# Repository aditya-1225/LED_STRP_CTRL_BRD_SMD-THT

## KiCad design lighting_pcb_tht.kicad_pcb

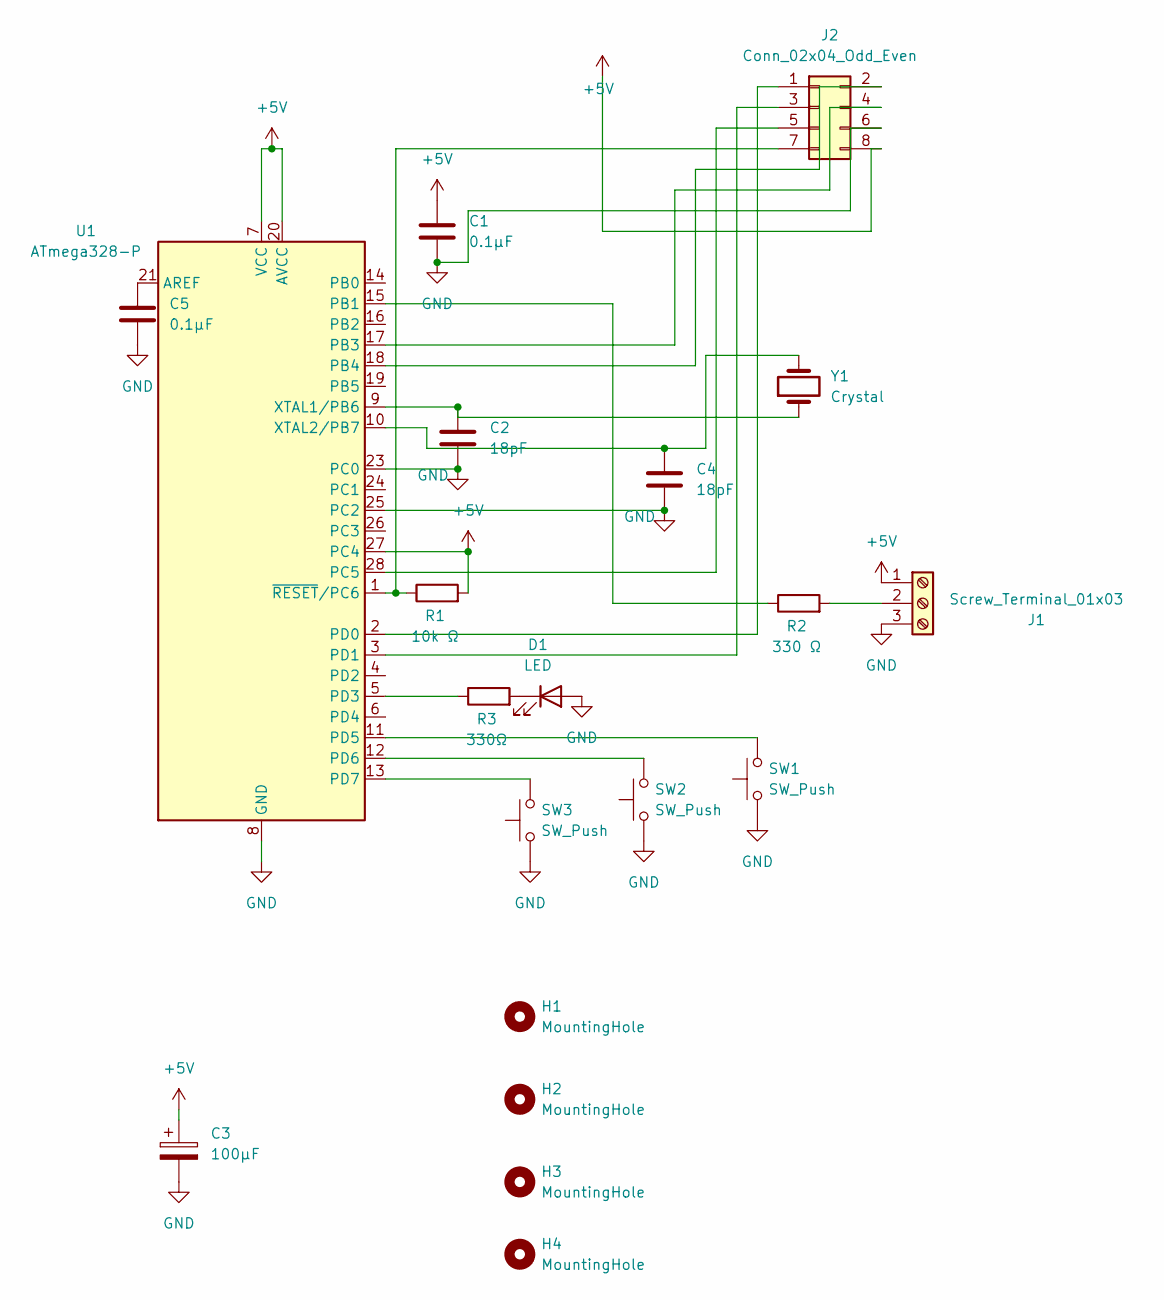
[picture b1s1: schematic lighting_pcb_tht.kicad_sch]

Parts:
C1, C5: 0.1μF; C_1206_3216Metric_Pad1.33x1.80mm_HandSolder
C2, C4: 18pF; C_1206_3216Metric_Pad1.33x1.80mm_HandSolder
C3: 100μF; CP_Radial_D5.0mm_P2.00mm
D1: LED; LED_1206_3216Metric_Pad1.42x1.75mm_HandSolder
H1, H2, H3, H4: MountingHole; MountingHole_2mm
J1: Screw_Terminal_01x03; TerminalBlock_MaiXu_MX126-5.0-03P_1x03_P5.00mm
J2: Conn_02x04_Odd_Even; PinHeader_2x04_P2.54mm_Vertical
R1: 10k Ω; R_1206_3216Metric_Pad1.30x1.75mm_HandSolder
R2: 330 Ω; R_1206_3216Metric_Pad1.30x1.75mm_HandSolder
R3: 330Ω; R_1206_3216Metric_Pad1.30x1.75mm_HandSolder
SW1, SW2, SW3: SW_Push; SW_PUSH-12mm
U1: ATmega328-P; DIP-28_W7.62mm_Socket
Y1: Crystal; Crystal_HC49-U_Vertical

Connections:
+5V: C1.1, C3.1, J1.1, J2.8, R1.2, U1.7 (VCC), U1.20 (AVCC), U1.27 (PC4)
GND: C1.2, C2.2, C3.2, C4.2, C5.2, D1.2 (A), J1.3, J2.6, SW1.1, SW2.1, SW3.1, U1.8 (GND), U1.22 (GND), U1.23 (PC0), U1.25 (PC2)
unnamed: D1.1 (K), R3.2
unnamed: J1.2, R2.2
unnamed: J2.1, U1.2 (PD0)
unnamed: J2.2, U1.18 (PB4)
unnamed: J2.3, U1.3 (PD1)
unnamed: J2.4, U1.17 (PB3)
unnamed: J2.5, U1.28 (PC5)
unnamed: J2.7, R1.1, U1.1 (~RESET/PC6)
unnamed: C5.1, U1.21 (AREF)
unnamed: R2.1, U1.15 (PB1)
unnamed: R3.1, U1.5 (PD3)
unnamed: SW1.2, U1.11 (PD5)
unnamed: SW2.2, U1.12 (PD6)
unnamed: SW3.2, U1.13 (PD7)
unnamed: C2.1, U1.9 (XTAL1/PB6), Y1.1
unnamed: C4.1, U1.10 (XTAL2/PB7), Y1.2

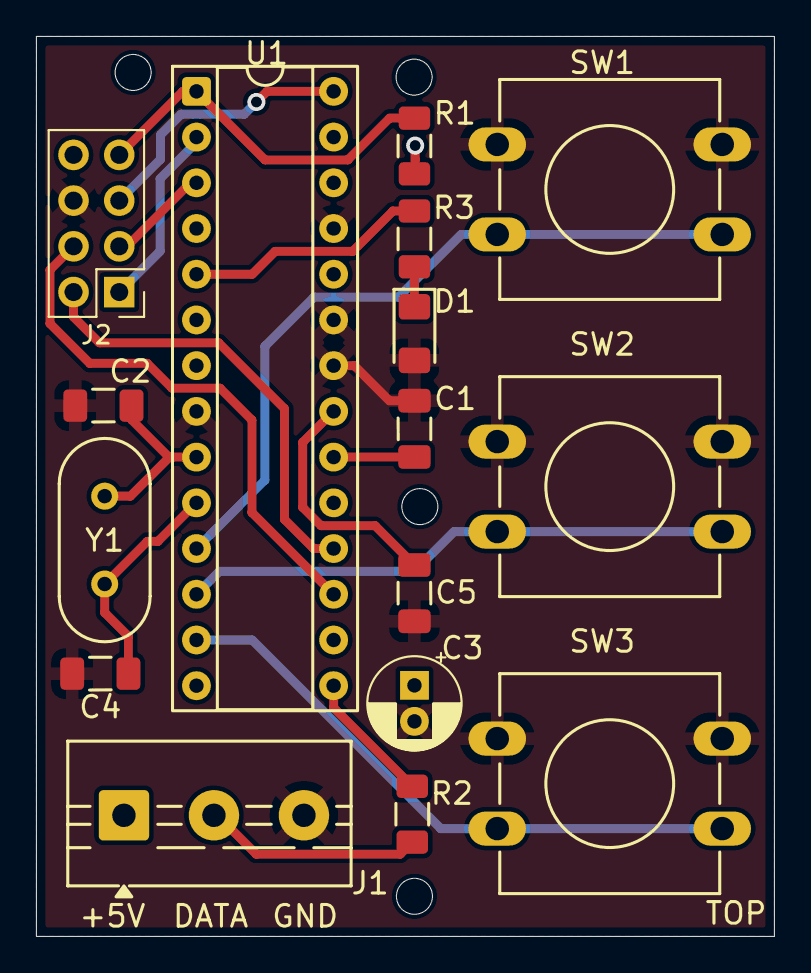
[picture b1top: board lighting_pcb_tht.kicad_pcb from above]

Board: 2 copper layers, 41.0 x 50.0 mm, 20 parts (0 on the bottom side), 18 nets.

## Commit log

2025-06-29 Changed the pads used for programming to header pins
2025-07-16 Final design with THT chip and SMD res/caps
